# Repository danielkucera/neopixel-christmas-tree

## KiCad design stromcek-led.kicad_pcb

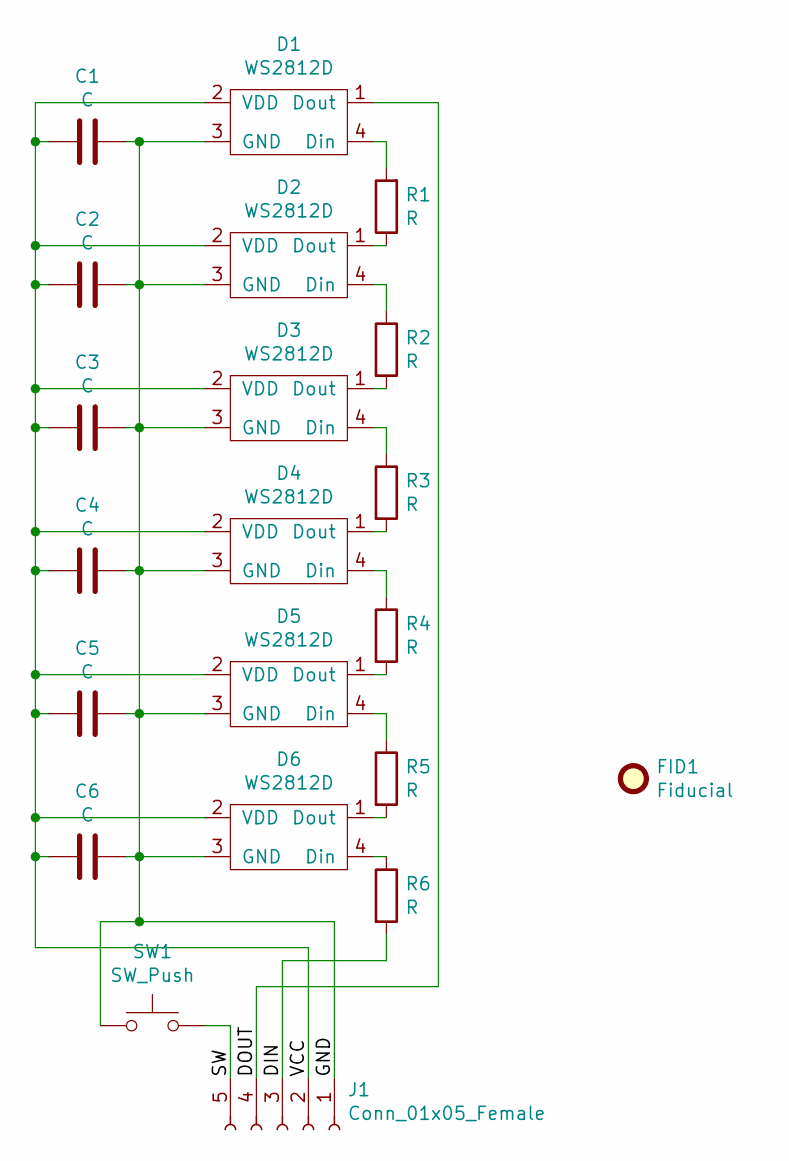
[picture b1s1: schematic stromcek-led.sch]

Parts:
C1, C2, C3, C4, C5, C6: C; C_Disc_D5.0mm_W2.5mm_P2.50mm
D1, D2, D3, D4, D5, D6: WS2812D
FID1: Fiducial; ozdoby
J1: Conn_01x05_Female; PinSocket_1x05_P2.54mm_Horizontal
R1, R2, R3, R4, R5, R6: R; R_Axial_DIN0207_L6.3mm_D2.5mm_P10.16mm_Horizontal
SW1: SW_Push; SW_DIP_SPSTx01_Slide_6.7x4.1mm_W6.73mm_P2.54mm_LowProfile_J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

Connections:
/DIN: J1.3, R6.2
/DOUT: D1.1 (Dout), J1.4
/GND: C1.1, C2.2, C3.1, C4.1, C5.1, C6.1, D1.3 (GND), D2.3 (GND), D3.3 (GND), D4.3 (GND), D5.3 (GND), D6.3 (GND), J1.1, SW1.1
/SW: J1.5, SW1.2
/VCC: C1.2, C2.1, C3.2, C4.2, C5.2, C6.2, D1.2 (VDD), D2.2 (VDD), D3.2 (VDD), D4.2 (VDD), D5.2 (VDD), D6.2 (VDD), J1.2
unnamed: D1.4 (Din), R1.2
unnamed: D2.1 (Dout), R1.1
unnamed: D2.4 (Din), R2.1
unnamed: D3.1 (Dout), R2.2
unnamed: D3.4 (Din), R3.1
unnamed: D4.1 (Dout), R3.2
unnamed: D4.4 (Din), R4.1
unnamed: D5.1 (Dout), R4.2
unnamed: D5.4 (Din), R5.1
unnamed: D6.1 (Dout), R5.2
unnamed: D6.4 (Din), R6.1

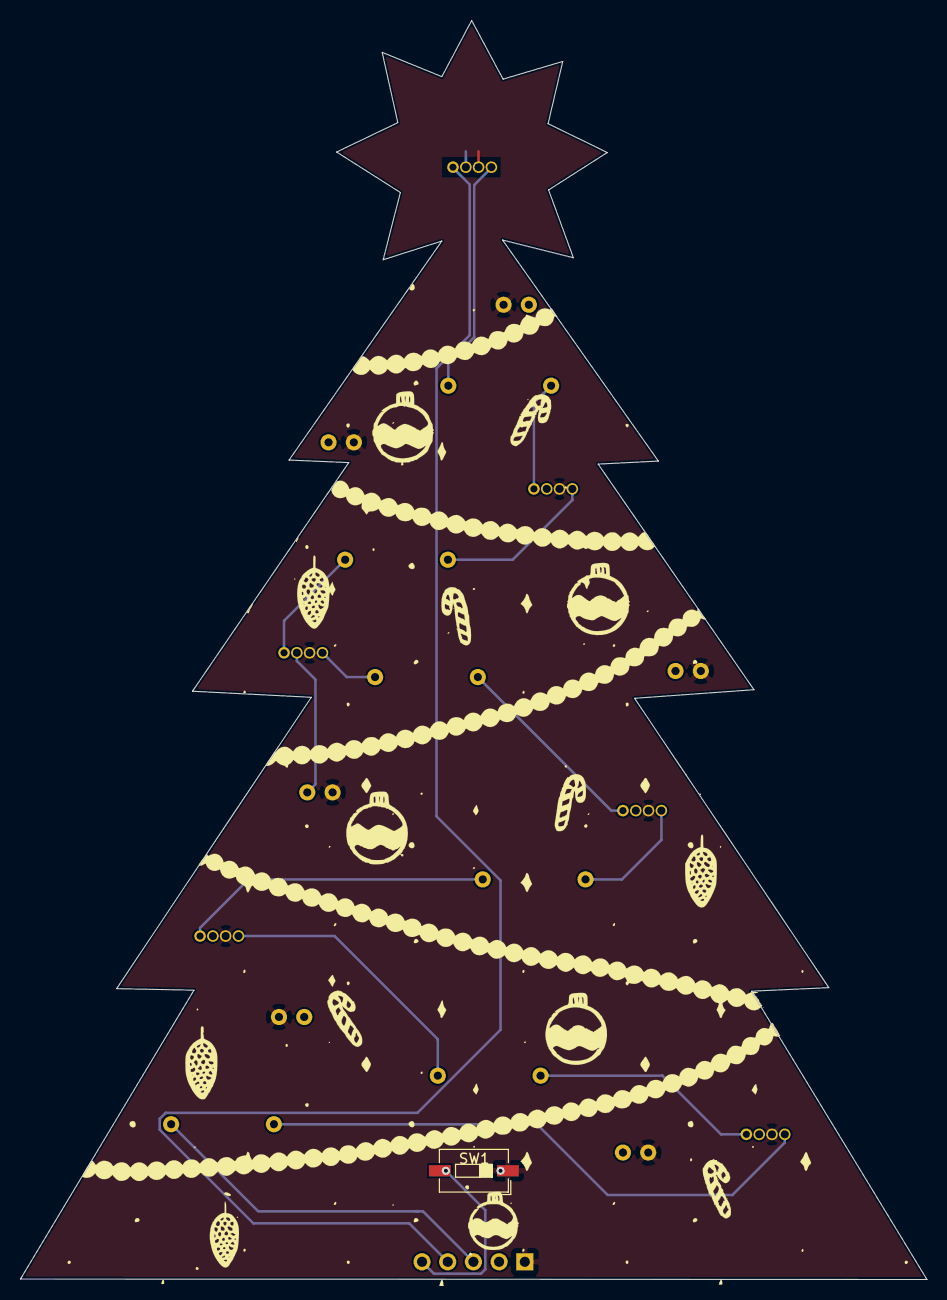
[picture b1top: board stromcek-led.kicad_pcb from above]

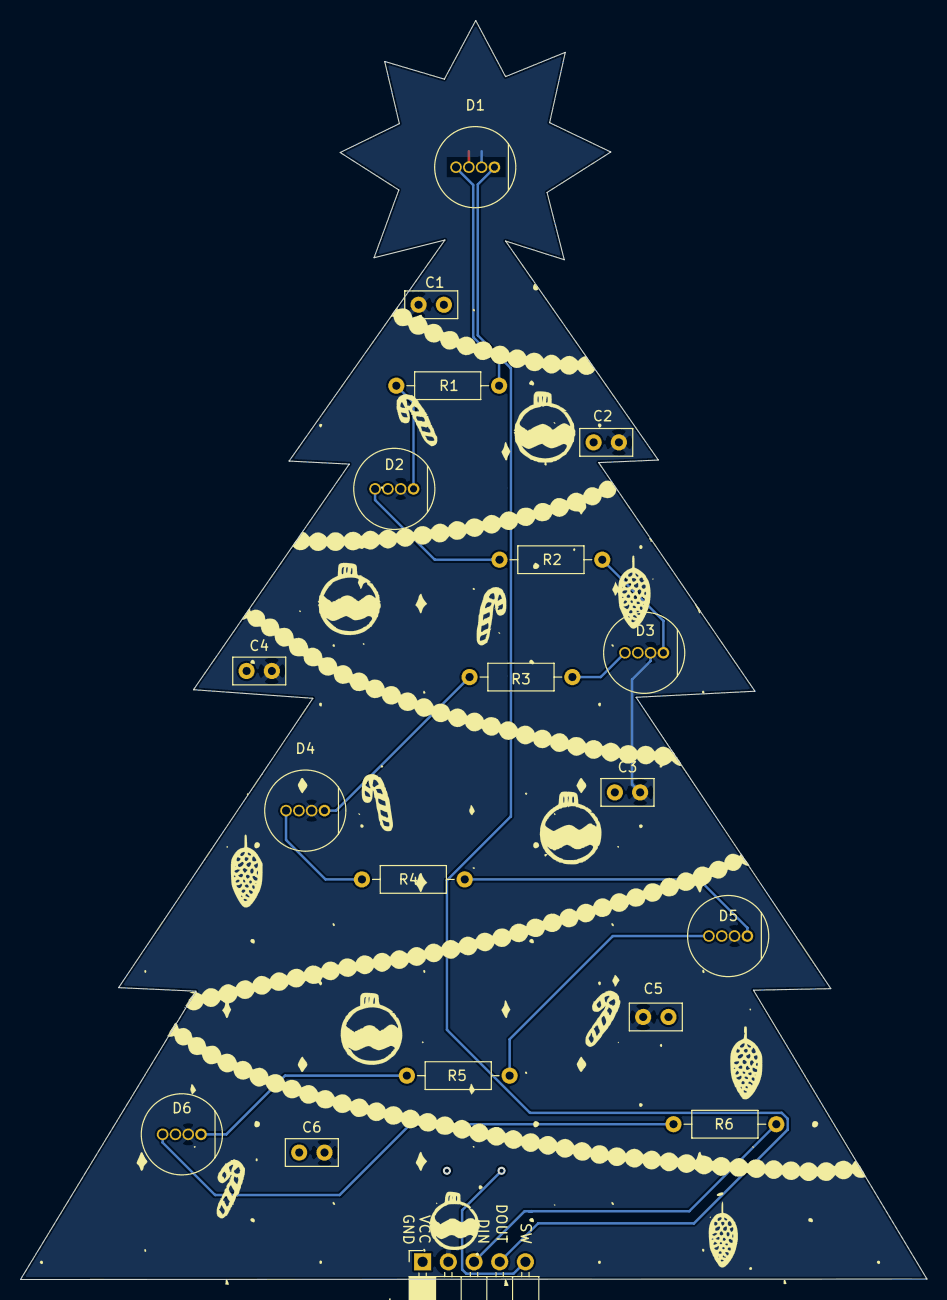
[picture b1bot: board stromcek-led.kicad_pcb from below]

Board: 2 copper layers, 89.6 x 124.4 mm, 21 parts (19 on the bottom side), 16 nets.

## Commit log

2021-11-28 first prototype
2021-12-17 fixed D1 VCC, C1 crossing track, keepout on D1
